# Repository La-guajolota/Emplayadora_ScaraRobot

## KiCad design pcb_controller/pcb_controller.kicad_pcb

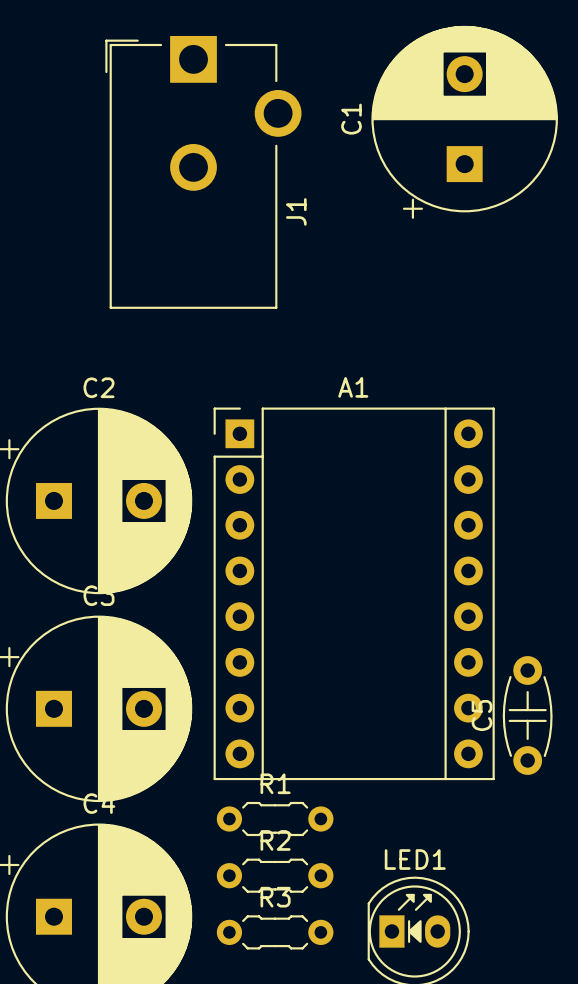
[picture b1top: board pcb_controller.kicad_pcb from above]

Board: 2 copper layers, 11 parts (0 on the bottom side), 4 nets, no tracks yet.

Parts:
A1: Pololu_Breakout_DRV8825; Pololu_Breakout-16_15.2x20.3mm
C1, C2, C3, C4: 22uF 48v; CP_Radial_D10.0mm_P5.00mm
C5: 100nF; C_Disc_D4.7mm_W2.5mm_P5.00mm
J1: Barrel_Jack_Switch; BarrelJack_CUI_PJ-102AH_Horizontal
LED1: Red; LED_D5.0mm
R1, R2: 4K7; R_Axial_DIN0204_L3.6mm_D1.6mm_P5.08mm_Horizontal
R3: 1K; R_Axial_DIN0204_L3.6mm_D1.6mm_P5.08mm_Horizontal

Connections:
+3.3V: R1.1, R2.1
+12V: A1.8 (VMOT), C1.1, C2.1, C3.1, C4.1, J1.1, R3.1
GNDA: A1.7 (GND), C1.2, C2.2, C3.2, C4.2, J1.2, J1.3, LED1.1 (K)
unnamed: LED1.2 (A), R3.2

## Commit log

2025-04-25 SCARA primera carga
2025-05-02 primer commit pcb diseño
2025-05-02 original 3d models
2025-05-06 pixels to in
